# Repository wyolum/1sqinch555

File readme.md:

# 1sqinch555
3x3x3 LED cube without using microcontroller.
Uses the awesome 555 timer and a 14 bit ripple counter (4020).
9 outputs from the counter drive sets of 3 LEDs in series.
Works off 9V battery.
Possible submission for 1 square inch competition at HAD.

License
-------
[CERN Open Hardware Licence v1.2 ]

[CERN Open Hardware Licence v1.2 ]:http://www.ohwr.org/attachments/2388/cern_ohl_v_1_2.txt

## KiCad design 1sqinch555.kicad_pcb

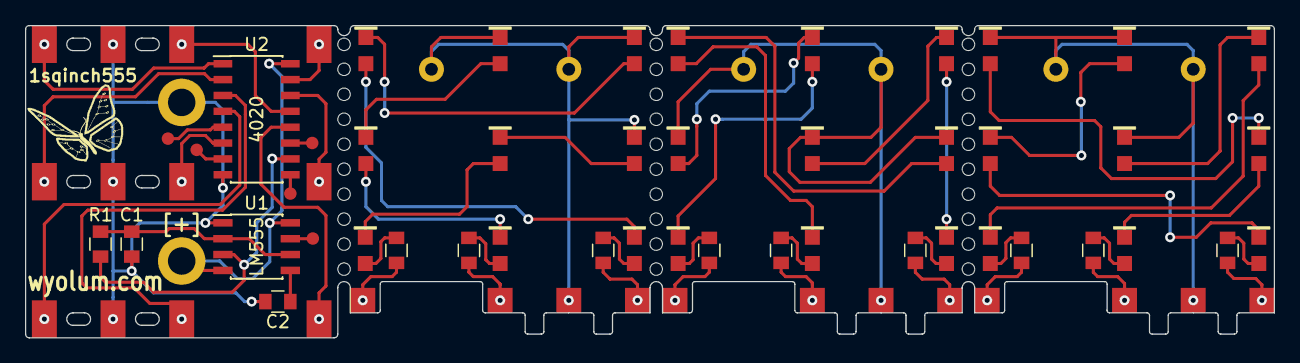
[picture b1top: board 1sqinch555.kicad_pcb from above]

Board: 2 copper layers, 100.0 x 25.0 mm, 78 parts (0 on the bottom side), 58 nets.

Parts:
BT1: 9V; 9V_clip_968
C1: 10uF; C_0805
C2: 10nF; C_0805
D1, D2, D3, D4, D5, D6, D7, D8, D9, D10, D11, D12, D13, D14, D15, D16, D17, D18, D19, D20, D21, D22, D23, D24, D25, D26, D27: LED; LED-0805
G1: Logo-WL3
J1, J2, J3, J4, J5: Conn_01x01; pad_smd_1mm
J6, J8, J10, J12, J14, J16, J18, J20, J22, J24, J26, J28: Conn_01x01; pad_3x2mm_smd
J7, J9, J11, J13, J15, J17, J19, J21, J23, J25, J27, J29: Conn_01x01; pad_2x2mm
J30, J31, J32, J33, J34, J35: Conn_01x01; Plated_Hole_d1.0mm
R1: 33k; R_0805
R2, R3, R4, R5, R6, R7, R8, R9, R10: 300; R_0805
U1: LM555; SOIC-8_3.9x4.9mm_Pitch1.27mm
U2: 4020; SOIC-16_3.9x9.9mm_Pitch1.27mm

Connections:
/5: J23.1, R10.2
/6: J15.1, R6.2
/7: J9.1, R3.2
/8: J19.1, R8.2
/9: J13.1, R5.2
/9V: BT1.1, U1.4, U1.8, U2.16
/10: J7.1, R2.2
/11: J11.1, R4.2
/12: J17.1, R7.2
/13: J21.1, R9.2
/CV: C2.1, U1.5
/GND: BT1.2, C1.2, C2.2, J24.1, J26.1, J28.1, U1.1, U2.8
/GND1: D3.1, D6.1, D9.1, J25.1, J30.1, J31.1
/GND2: D12.1, D15.1, D18.1, J27.1, J32.1, J33.1
/GND3: D21.1, D24.1, D27.1, J29.1, J34.1, J35.1
/OUT: R1.1, U1.3, U2.10
/Q0: J2.1, U2.9
/Q3: J3.1, U2.7
/Q4: J5.1, U2.5
/Q5: J6.1, U2.4
/Q6: J8.1, U2.6
/Q7: J10.1, U2.13
/Q8: J12.1, U2.12
/Q9: J14.1, U2.14
/Q10: J16.1, U2.15
/Q11: J18.1, U2.1
/Q12: J20.1, U2.2
/Q13: J22.1, U2.3
/RST: J4.1, U2.11
/TR: C1.1, R1.2, U1.2, U1.6
unnamed: D1.1, D2.2
unnamed: D1.2, R2.1
unnamed: D2.1, D3.2
unnamed: D4.1, D5.2
unnamed: D4.2, R3.1
unnamed: D5.1, D6.2
unnamed: D7.1, D8.2
unnamed: D7.2, R4.1
unnamed: D8.1, D9.2
unnamed: D10.1, D11.2
unnamed: D10.2, R5.1
unnamed: D11.1, D12.2
unnamed: D13.1, D14.2
unnamed: D13.2, R6.1
unnamed: D14.1, D15.2
unnamed: D16.1, D17.2
unnamed: D16.2, R7.1
unnamed: D17.1, D18.2
unnamed: D19.1, D20.2
unnamed: D19.2, R8.1
unnamed: D20.1, D21.2
unnamed: D22.1, D23.2
unnamed: D22.2, R9.1
unnamed: D23.1, D24.2
unnamed: D25.1, D26.2
unnamed: D25.2, R10.1
unnamed: D26.1, D27.2
unnamed: J1.1, U1.7

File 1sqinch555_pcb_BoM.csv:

"Id";"Designator";"Package";"Quantity";"Designation";"Supplier and ref";
1;"D1,D2,D3,D4,D5,D6,D7,D8,D9,D10,D11,D12,D13,D14,D15,D16,D17,D18,D19,D20,D21,D22,D23,D24,D25,D26,D27";"LED-0805";27;"LED";;;
2;"J3,J1,J2,J4,J5";"pad_smd_1mm";5;"Conn_01x01";;;
3;"R3,R2,R4,R5,R6,R7,R8,R9,R10";"R_0805";9;"300";;;
4;"C2";"C_0805";1;"10nF";;;
5;"J6,J8,J10,J12,J14,J16,J18,J20,J22,J24,J26,J28";"pad_3x2mm_smd";12;"Conn_01x01";;;
6;"mouse-bite-2.5mm-slot,mouse-bite-2.5mm-slot,mouse-bite-2.5mm-slot,mouse-bite-2.5mm-slot,mouse-bite-2.5mm-slot,mouse-bite-2.5mm-slot";"mouse-bite-2.5mm-slot";6;"VAL**";;;
7;"BT1";"9V_clip_968";1;"9V";;;
8;"J7,J9,J11,J13,J15,J17,J19,J21,J23,J25,J27,J29";"pad_2x2mm";12;"Conn_01x01";;;
9;"U1";"SOIC-8_3.9x4.9mm_Pitch1.27mm";1;"LM555";;;
10;"U2";"SOIC-16_3.9x9.9mm_Pitch1.27mm";1;"4020";;;
11;"J30,J31,J32,J33,J34,J35";"Plated_Hole_d1.0mm";6;"Conn_01x01";;;
12;"G1";"Logo-WL3";1;"Logo-WL3";;;
13;"C1";"C_0805";1;"10uF";;;
14;"R1";"R_0805";1;"33k";;;

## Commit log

2018-08-12 initial commit, a 1 sq inch 555 timer project
2018-08-12 added schematic to pdf folder
2018-08-12 regenerated gerbers
2018-08-13 BoM update
2018-08-13 changed 0603 to 0805
2018-08-14 mods
2018-08-14 layout changes
2018-08-17 BoM updates
2018-08-21 randomizing LEDs
2018-08-23 1mm PCB thickness
